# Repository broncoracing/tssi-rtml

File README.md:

# TSSI, Ready to move light, and Voltage Indicator
Tractive system active light for BR25

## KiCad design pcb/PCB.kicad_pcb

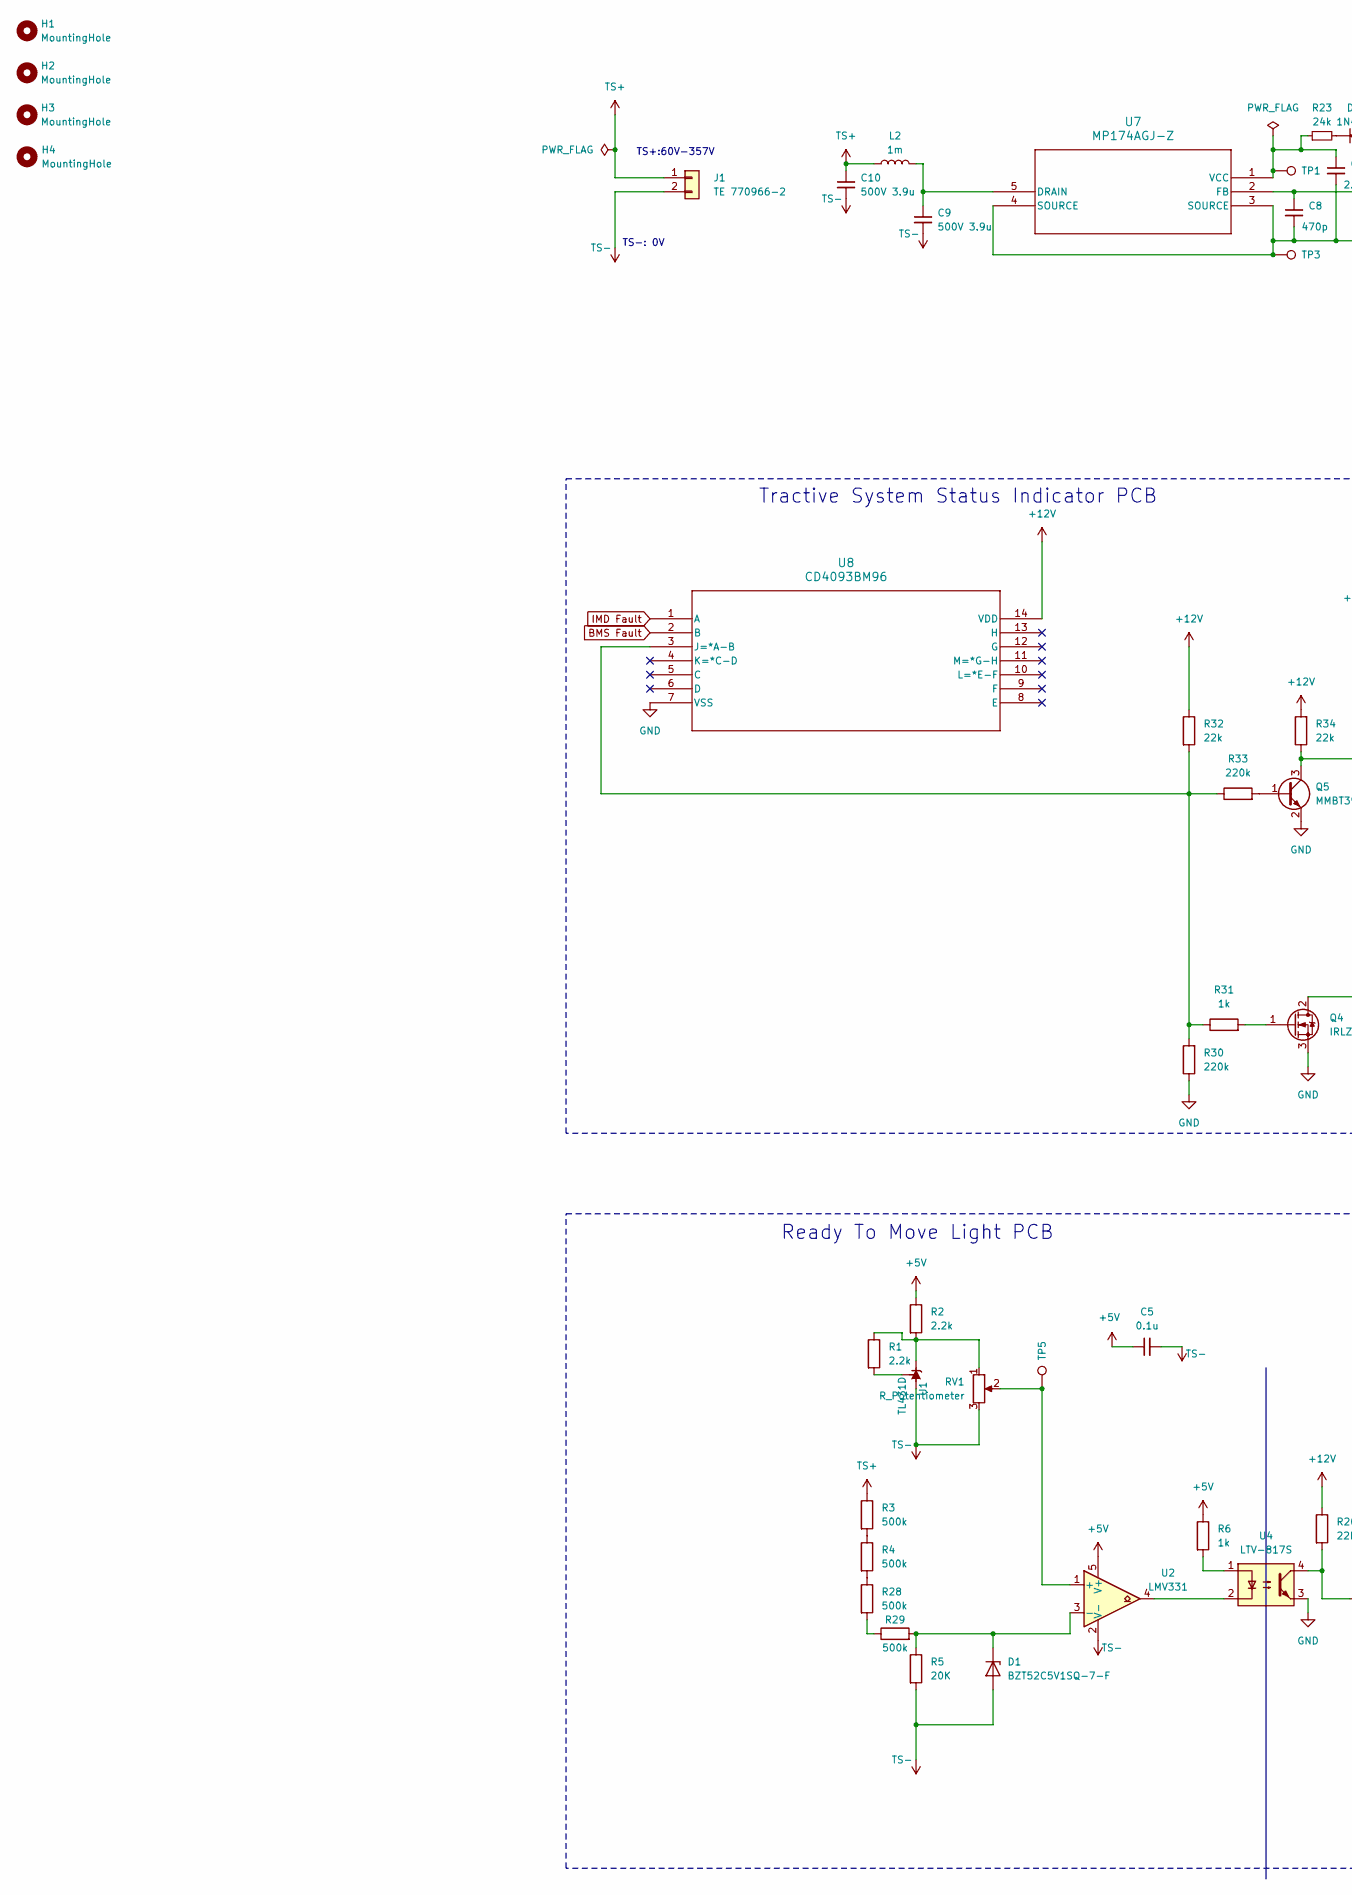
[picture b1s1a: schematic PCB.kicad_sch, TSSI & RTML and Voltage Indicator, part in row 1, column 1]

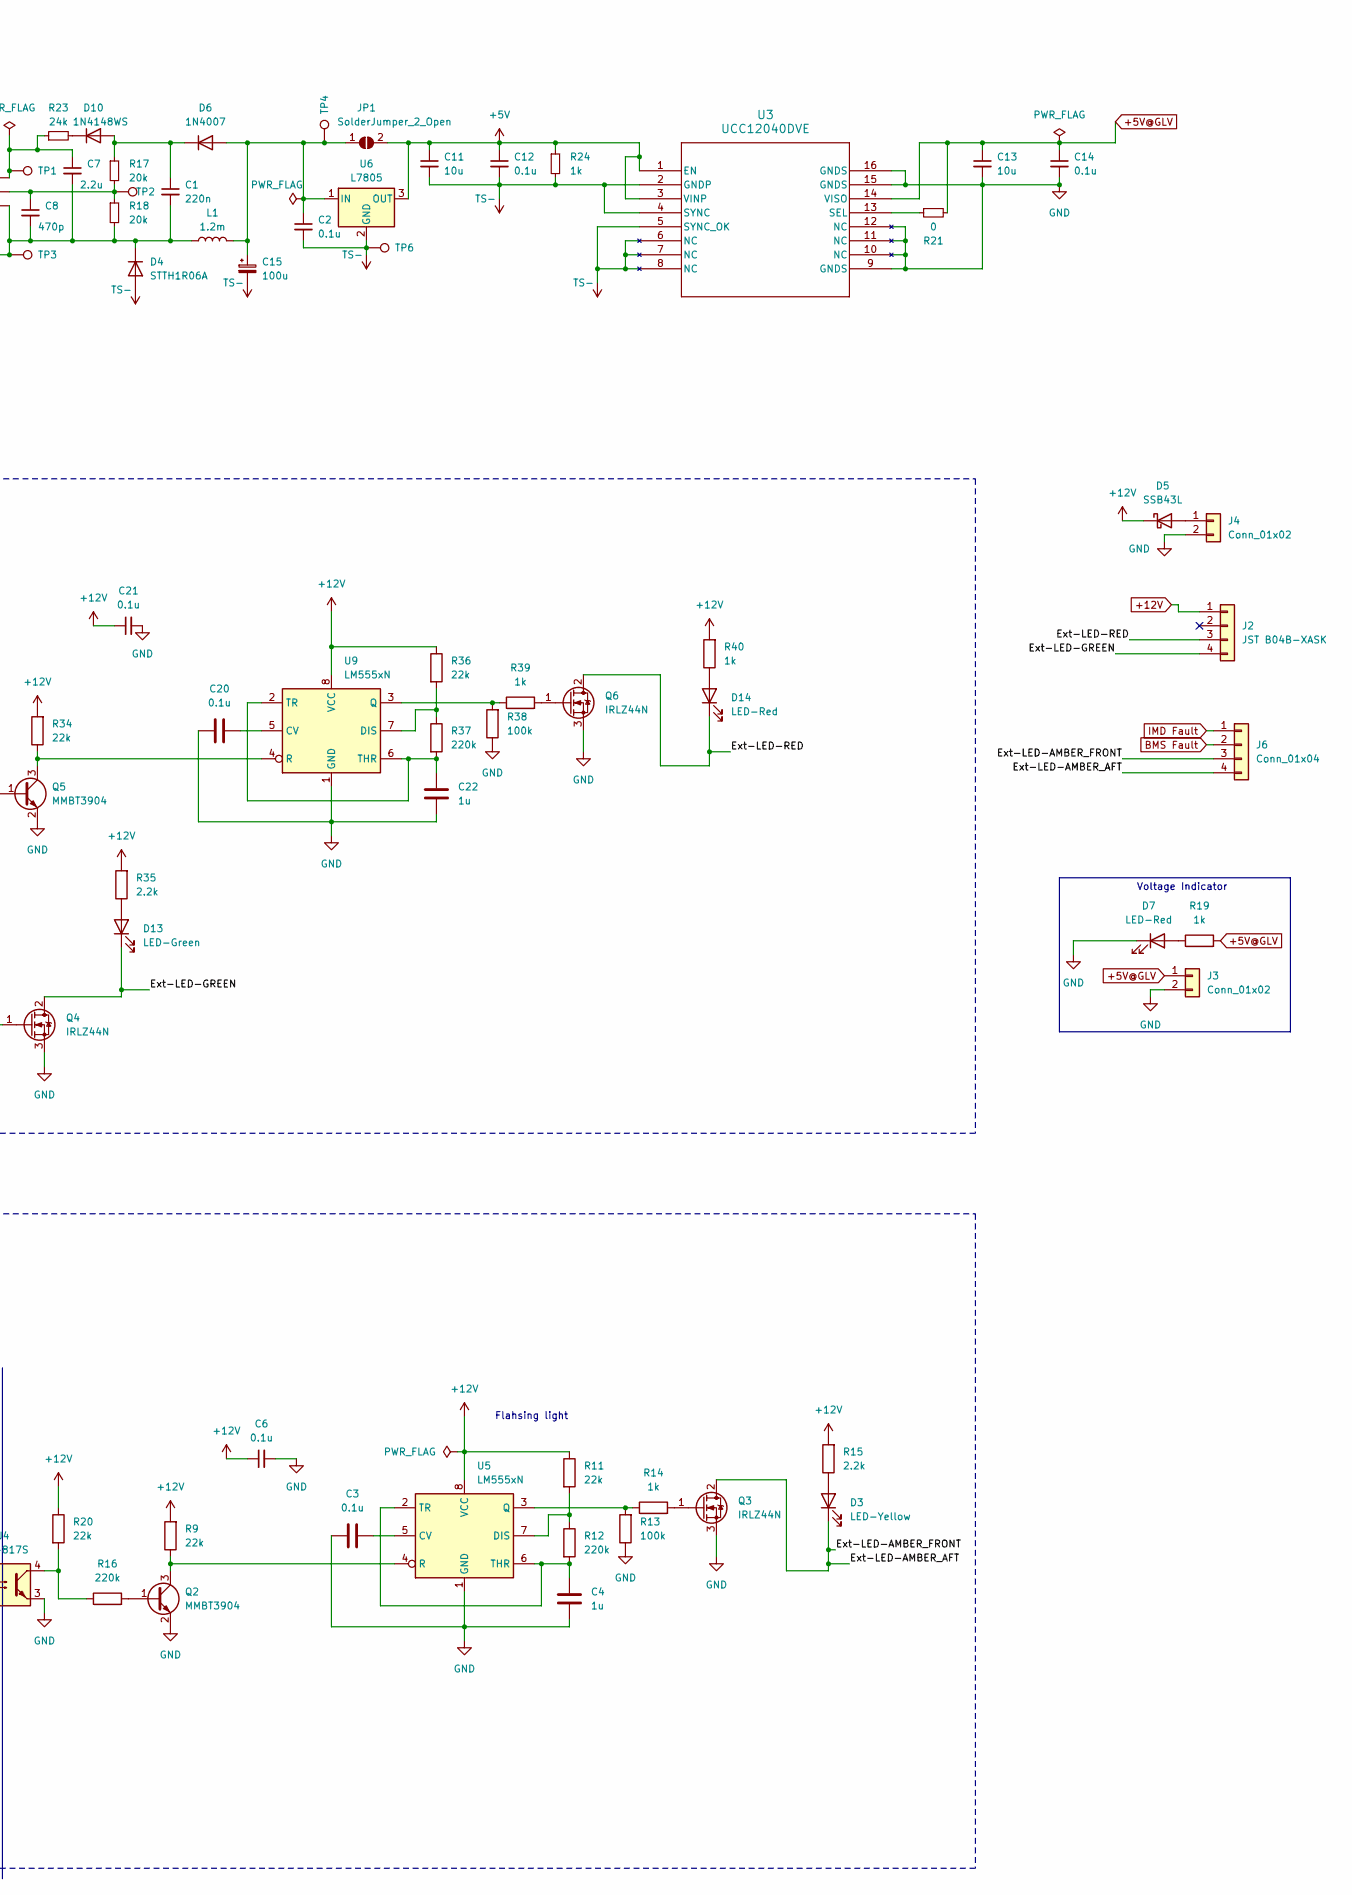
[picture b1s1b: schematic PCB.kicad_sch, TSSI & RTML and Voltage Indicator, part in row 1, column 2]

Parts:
C1: 220n; C_0603_1608Metric
C2, C3, C5, C6, C12, C14, C20, C21: 0.1u; C_0603_1608Metric
C4, C22: 1u; C_0603_1608Metric
C7: 2.2u; C_0603_1608Metric
C8: 470p; C_0603_1608Metric
C9, C10: 500V 3.9u; C_Elec_10x10.2
C11, C13: 10u; C_0603_1608Metric
C15: 100u; CP_Elec_6.3x7.7
D1: BZT52C5V1SQ-7-F; D_SOD-323F
D3: LED-Yellow; LED_0603_1608Metric
D4: STTH1R06A; D_SMA
D5: SSB43L; D_SMB
D6: 1N4007; D_SOD-123
D7, D14: LED-Red; LED_0603_1608Metric
D10: 1N4148WS; D_SOD-323
D13: LED-Green; LED_0603_1608Metric
H1, H2, H3, H4: MountingHole; MountingHole_3.2mm_M3
J1: TE 770966-2; TE_MATE-N-LOK_1-770966-x_1x02_P4.14mm_Horizontal
J2: JST B04B-XASK; JST_XA_B04B-XASK-1-A_1x04_P2.50mm_Vertical
J3, J4: Conn_01x02; TE_MATE-N-LOK_1-770966-x_1x02_P4.14mm_Horizontal
J6: Conn_01x04; TE_MATE-N-LOK_1-770968-x_2x02_P4.14mm_Horizontal
JP1: SolderJumper_2_Open; SolderJumper-2_P1.3mm_Open_RoundedPad1.0x1.5mm
L1: 1.2m; L_12x12mm_H8mm
L2: 1m; L_1210_3225Metric
Q2, Q5: MMBT3904; SOT-23
Q3, Q4, Q6: IRLZ44N; NMOSGDS_D2PAK_INF
R1, R2, R15, R35: 2.2k; R_0603_1608Metric
R3, R4, R28, R29: 500k; R_1206_3216Metric
R5: 20K; R_1206_3216Metric
R6, R14, R19, R24, R31, R39, R40: 1k; R_0603_1608Metric
R9, R11, R20: 22k; R_0603_1608Metric
R12, R16, R30, R33, R37: 220k; R_0603_1608Metric
R13, R38: 100k; R_0603_1608Metric
R17, R18: 20k; R_0603_1608Metric
R21: 0; R_0603_1608Metric
R23: 24k; R_0603_1608Metric
R32, R34, R36: 22k; R_0603_1608Metric; LCSC C23344
RV1: R_Potentiometer; Potentiometer_Bourns_3269W_Vertical
TP1, TP2, TP3, TP4, TP5, TP6: TestPoint; TestPoint_Keystone_5019_Minature
U1: TL431D; SOIC-8_3.9x4.9mm_P1.27mm
U2: LMV331; SOT-23-5
U3: UCC12040DVE; SO_0DVER_TEX
U4: LTV-817S; SMDIP-4_W9.53mm
U5, U9: LM555xN; M08A-L
U6: L7805; TO-252-2
U7: MP174AGJ-Z; TSOT23-5_MP174A_MNP
U8: CD4093BM96; SOIC-14_3.9x8.7mm_P1.27mm; LCSC C34809

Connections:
+5V: C5.1, C11.1, C12.1, JP1.2 (B), R2.1, R6.1, R24.1, U2.5 (V+), U3.1 (EN), U3.3 (VINP), U6.3 (OUT)
+5V@GLV: C13.1, C14.1, J3.1, R19.2, R21.2, U3.14 (VISO)
+12V: C6.1, C21.1, D5.1 (K), J2.1, R9.2, R11.1, R15.2, R20.1, R32.1, R34.2, R35.2, R36.1, R40.2, U5.8 (VCC), U8.14 (VDD), U9.8 (VCC)
/Ext-LED-AMBER_AFT: D3.1 (K), J6.3, J6.4, Q3.2 (D)
/Ext-LED-GREEN: D13.1 (K), J2.4, Q4.2 (D)
/Ext-LED-RED: D14.1 (K), J2.3, Q6.2 (D)
BMS Fault: J6.2, U8.2 (B)
GND: C3.1, C4.1, C6.2, C13.2, C14.2, C20.1, C21.2, C22.1, D7.1 (K), J3.2, J4.2, Q2.2 (E), Q3.3 (S), Q4.3 (S), Q5.2 (E), Q6.3 (S), R13.1, R30.1, R38.1, U3.9 (GNDS), U3.10 (NC), U3.11 (NC), U3.12 (NC), U3.15 (GNDS), U3.16 (GNDS), U4.3, U5.1 (GND), U8.7 (VSS), U9.1 (GND)
IMD Fault: J6.1, U8.1 (A)
unnamed: D1.1 (K), R5.1, R29.2, U2.3 (-)
unnamed: D3.2 (A), R15.1
unnamed: C1.2, C7.2, C8.2, D4.1 (K), L1.1, R18.2, TP3.1, U7.3 (SOURCE), U7.4 (SOURCE)
unnamed: D5.2 (A), J4.1
unnamed: C2.1, C15.1, D6.2 (A), JP1.1 (A), L1.2, TP4.1, U6.1 (IN)
unnamed: D7.2 (A), R19.1
unnamed: C1.1, D6.1 (K), D10.2 (A), R17.1
unnamed: D10.1 (K), R23.2
unnamed: D13.2 (A), R35.1
unnamed: D14.2 (A), R40.1
unnamed: Q2.1 (B), R16.2
unnamed: Q2.3 (C), R9.1, U5.4 (R)
unnamed: Q3.1 (G), R14.2
unnamed: Q4.1 (G), R31.2
unnamed: Q5.1 (B), R33.2
unnamed: Q5.3 (C), R34.1, U9.4 (R)
unnamed: Q6.1 (G), R39.2
unnamed: R3.2, R4.1
unnamed: R6.2, U4.1
unnamed: R16.1, R20.2, U4.4
unnamed: R4.2, R28.1
unnamed: R28.2, R29.1
unnamed: R1.1, R2.2, RV1.1, U1.1 (K)
unnamed: R1.2, U1.8 (REF)
unnamed: RV1.2, TP5.1, U2.1 (+)
unnamed: U2.4, U4.2
unnamed: R21.1, U3.13 (SEL)
unnamed: C3.2, U5.5 (CV)
unnamed: R11.2, R12.1, U5.7 (DIS)
unnamed: R13.2, R14.1, U5.3 (Q)
unnamed: C4.2, R12.2, U5.2 (TR), U5.6 (THR)
unnamed: C9.1, L2.2, U7.5 (DRAIN)
unnamed: C8.1, R17.2, R18.1, TP2.1, U7.2 (FB)
unnamed: C7.1, R23.1, TP1.1, U7.1 (VCC)
unnamed: R30.2, R31.1, R32.2, R33.1, U8.3 (J=*A-B)
unnamed: C20.2, U9.5 (CV)
unnamed: R36.2, R37.1, U9.7 (DIS)
unnamed: R38.2, R39.1, U9.3 (Q)
unnamed: C22.2, R37.2, U9.2 (TR), U9.6 (THR)
TS+: C10.1, J1.1, L2.1, R3.1
TS-: C2.2, C5.2, C9.2, C10.2, C11.2, C12.2, C15.2, D1.2 (A), D4.2 (A), J1.2, R5.2, R24.2, RV1.3, TP6.1, U1.2 (A), U1.3 (A), U1.6 (A), U1.7 (A), U2.2 (V-), U3.2 (GNDP), U3.4 (SYNC), U3.5 (SYNC_OK), U3.6 (NC), U3.7 (NC), U3.8 (NC), U6.2 (GND)

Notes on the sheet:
Flahsing light
TS+:60V-357V
Voltage Indicator
Tractive System Status Indicator PCB
Ready To Move Light PCB
TS-: 0V

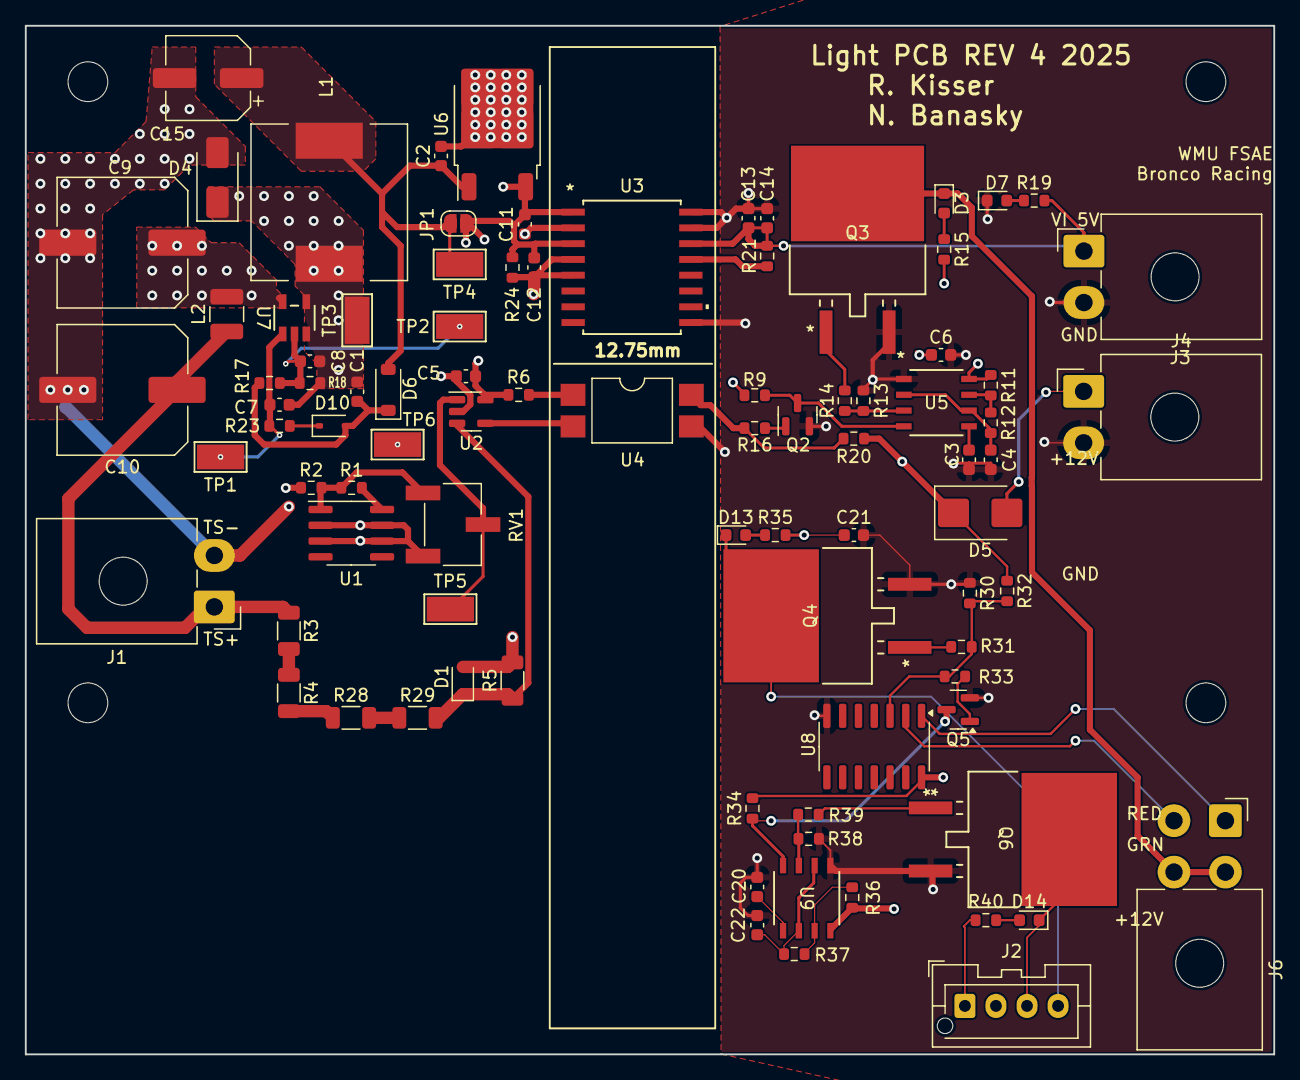
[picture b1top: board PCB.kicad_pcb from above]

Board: 4 copper layers, 100.5 x 82.8 mm, 93 parts (0 on the bottom side), 50 nets.

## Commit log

2022-09-30 Updated to new template
2024-01-24 Fix github action again (maybe?)
2024-01-24 TSAL W/ updated DC-DC + Meme
2024-01-24 TSAL and Voltage indicator schematic
2024-01-24 New TSAL
2024-01-24 TSAL V2
2024-01-24 fixed github action
2024-01-24 TSAL - meme
2024-01-24 Changed opto-isolator
2024-01-24 Removed TSAL.zip
2024-01-24 resisitor change
2024-01-24 Fixed drc violations
2024-01-24 added blah file
2024-01-24 Fixed git repo organization
2024-03-12 fix low voltage circuit
2024-03-13 TSAL REV3 :(
2024-03-13 TSAL V3 Minor changes
2024-03-13 Minor changes once again
2024-03-23 Footprint change
2024-03-24 Edit to PCB due to footprint change
2024-03-24 JP1 Edit
2025-01-06 TSSI/RTML/Voltage indicator Initial Commit
2025-04-10 TSSI update 3-29-25 initial
2025-04-10 Kicad 9 preparation
2025-05-10 For gerbers
